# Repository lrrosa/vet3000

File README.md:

# VET 3000 — engenharia reversa e cartucho de demonstração

O **VET 3000 "The Video Effects Titler"** é um titulador de vídeo brasileiro fabricado pela
**TMS – Tecnologia em Micro Sistemas** (firmware © 1988, 1989). Por dentro, ele é um microcomputador:
CPU **Motorola MC6809**, processador de vídeo **Texas TMS9128** (família do TMS9918 usado no MSX 1 e
no ColecoVision), 16 KB de VRAM, 8 KB de RAM estática com bateria e 16 KB de ROM. O projeto deriva
do **Video Titler** publicado na revista americana *Radio-Electronics* em 1985-1986, vendido nos
EUA como **MFJ-1480B "Video Effects Titler (VET)"**.

Este repositório reúne tudo o que foi levantado sobre o aparelho:

- **Hardware:** fotos da placa, lista de componentes, mapa de memória, pinagem do conector
  traseiro CN1 e matriz do teclado.
- **Firmware v2.1:** *disassembly* completo e comentado, que **remonta byte a byte idêntico** à EPROM
  original.
- **Interface de cartucho:** o firmware procura cartuchos `"OBJECT"` e `"FONT"` no conector
  traseiro durante o boot. Aqui está documentado como escrever programas para ele.
- **Cartucho de demonstração**, com abertura animada e o jogo **QUEBRA-TIJOLO**, testado no MAME.
- **Placa do cartucho** em KiCad 10 (esquemático, placa roteada com Freerouting, Gerbers prontos),
  com EPROM 27C128 e soquete de borda para o CN1.
- **Esquema aproximado da placa principal** em KiCad 10: a parte digital, com cada ligação marcada
  como medida no aparelho ou tirada da revista, e um roteiro de continuidade.
- **Ferramentas:** disassembler 6809 com rastreamento, script Lua que simula o cartucho no MAME sem
  recompilá-lo, e um patch para o driver do MAME.

| Titulador original (MAME) | Demo: abertura | Demo: jogo |
|---|---|---|
|  |  |  |

## Principais descobertas

- **Origem:** o VET 3000 é uma versão do "Build This Video Titler", de Jack Flack
  (*Radio-Electronics*, 11/1985 a 03/1986), que a MFJ vendia como MFJ-1480B. Coincidem os CIs, o
  mapa de memória, a decodificação, a ordem dos pinos do CN1, o teclado, os registradores do VDP, os
  comandos, a abertura e a fonte. O esquema da revista explica a parte analógica e o PLL que gera o
  clock de 10,738635 MHz do VDP. O CI raspado U19 é um processador de croma CA3126 (confirmado pelas ligações). Ver
  [docs/origem.md](docs/origem.md).
- **Memória:** RAM em `$0000-$1FFF` (8 KB — a HY6264 tem 64 Kbit), cartucho em `$4000-$7FFF`,
  E/S em `$8000-$8002` e ROM em `$C000-$FFFF`. Detalhes em [docs/mapa-de-memoria.md](docs/mapa-de-memoria.md).
- **Boot automático de cartucho:** no boot, a ROM compara `"OBJECT"` em `$4000` (e depois em `$6000`)
  e executa `LDX [base+6]` / `JSR base,X`. Como o indireto lê duas vezes, `base+6` precisa conter um
  *ponteiro* para a palavra com o deslocamento da entrada. Cartuchos `"FONT"` substituem as fontes.
  Ver [docs/programando-cartuchos.md](docs/programando-cartuchos.md).
- **Uso da RAM:** o firmware nunca habilita interrupções. Os vetores de IRQ/SWI apontam para RAM
  (`$0039/$003B/$003D`) e existem só para os cartuchos. Os títulos ficam em `$00A0-$018F` e
  `$0200-$1FFF` (30 páginas); um cartucho pode rodar sem apagá-los.
- **Sem interrupção de quadro:** o `/INT` do VDP não está ligado ao `/IRQ` do 6809 (medido). Para
  sincronizar com o quadro, é preciso ler o status do VDP em laço. O driver do MAME 0.289 liga os
  dois, então um programa que dependa dessa interrupção roda no emulador e trava no aparelho. O
  patch em [mame/](mame/) corrige isso.
- **Código enxuto:** o código ocupa só cerca de 4,5 KB. O resto da ROM são três fontes (16×24, 8×24 e
  8×8), sprites e o logotipo. Há **3,2 KB livres** na EPROM.
- **Tecla "C" amarela:** não tem função no firmware v2.1 (a coluna dos modificadores só é lida nas
  linhas 1, 2 e 7, e o "C" amarelo fica na linha 6).
- **Bug no MAME 0.289:** o driver `vet3000` usa 3,58 MHz como clock do TMS9128. A tela roda a **20 Hz**
  em vez de 60 Hz. Há um patch em [mame/](mame/).

## Estrutura

```
docs/                 documentação (hardware, origem, memória, CN1, teclado, firmware, cartuchos, MAME)
  img/                fotos reduzidas, fontes extraídas da ROM e capturas de tela
  medidas-originais/  anotações originais da pinagem do CN1 e do teclado
photos/               fotos originais em alta resolução
rom/                  dump da EPROM 27128 (VET 2.1), preservado como material histórico
jogar_no_mame.bat     roda a demo no MAME (Windows)
disasm/               disassembly comentado (vet3000_v2.1.asm), anotações (hints.py), cobertura
tools/                dis6809.py, m6809.py, render_rom_gfx.py, show.py; mame/ (script Lua do cartucho)
cartridge/demo/       fonte do cartucho de demonstração (asm6809) e imagem pronta para a EPROM
mame/                 patch do driver vet3000 (slot de cartucho + clock correto do VDP)
hardware/cartucho/    projeto KiCad do cartucho (EPROM 27C128), Gerbers e scripts geradores
hardware/placa-principal/  esquema aproximado da placa principal (KiCad), roteiro de continuidade
```

## Uso rápido

Requisitos: Python 3 (com Pillow para as imagens) e o [asm6809](https://www.6809.org.uk/asm6809/).

**Conferir o disassembly** (gera o `.asm` e remonta; o resultado tem que ser idêntico à ROM):

```bash
python tools/dis6809.py rom/VET2.1-TMS_VET3000_27128A.BIN --hints disasm/hints.py -o disasm/vet3000_v2.1.asm
asm6809 -B -o /tmp/vet.bin disasm/vet3000_v2.1.asm && cmp /tmp/vet.bin rom/VET2.1-TMS_VET3000_27128A.BIN
```

**Montar o cartucho** (gera `build/vet3000_demo.bin`, com 16 KB, para uma EPROM 27128):

```bash
cd cartridge/demo && ./build.sh          # ou .\build.ps1 no Windows
```

**Rodar no MAME**, sem recompilar: o script Lua simula o cartucho no conector CN1. No Windows,
basta dar dois cliques em **`jogar_no_mame.bat`**. Ele prefere o build corrigido em
`../mame-build/vet.exe`, quando disponível, para rodar a aproximadamente 60 Hz.
Isso reduz os saltos da raquete de 9 para 3 pixels por quadro, mantendo a velocidade.
Para escolher outro MAME, passe o caminho como argumento ou defina a variável `MAME`.
Sem o build local, usa o caminho padrão configurado no `.bat`. O `.bat` chama:

```powershell
.\tools\mame\run_cart.ps1 -Mame C:\mame\mame.exe -Cart cartridge\demo\vet3000_demo.bin
```

Controles da demo: **ESPAÇO** joga, **Z/X** (ou O/P, ou ←→ com e sem SHIFT) movem a raquete,
**RETURN** pausa, **V** sobrepõe ao vídeo externo e **EXT MODE** volta ao titulador. Segurar
**EXT MODE** ao ligar pula o cartucho. No editor do titulador, **CONTROL+BORDER BLK** volta à demo
(no MAME, Ctrl esquerdo + vírgula).

## Documentação

1. [Hardware](docs/hardware.md): placa, componentes, clocks, vídeo, fonte
2. [Origem](docs/origem.md): o Video Titler da *Radio-Electronics* e o MFJ-1480B, comparação completa
3. [Mapa de memória](docs/mapa-de-memoria.md): CPU, E/S, VRAM, variáveis de RAM, ROM
4. [Conector CN1 e cartucho](docs/conector-cn1.md): pinagem e circuito de um cartucho com 27C128
5. [Teclado](docs/teclado.md): matriz, códigos, modificadores, leitura por software
6. [Firmware v2.1](docs/firmware.md): boot, laço principal, comandos, conjunto de caracteres, fontes
7. [Programando cartuchos](docs/programando-cartuchos.md): cabeçalho, regras de RAM, temporização do VDP
8. [MAME](docs/mame.md): como rodar, script Lua, bugs encontrados e patch do driver
9. [Cartucho de demonstração](cartridge/demo/README.md): técnicas, orçamento de ciclos, controles
10. [Placa do cartucho (KiCad)](hardware/cartucho/README.md): circuito, jumpers, montagem, fabricação
11. [Esquema da placa principal (KiCad)](hardware/placa-principal/README.md): parte digital e roteiro de continuidade

## Licença

Copyright © 2026 **Leonardo Roman da Rosa**.

Ferramentas, anotações do disassembly, documentação e o cartucho de demonstração são software livre
sob a **GNU General Public License versão 3** ou (a seu critério) qualquer versão posterior. Veja
[LICENSE](LICENSE).

O projeto de hardware do cartucho ([hardware/cartucho](hardware/cartucho/)) é hardware aberto sob a
**CERN-OHL-S-2.0** ([hardware/cartucho/LICENSE](hardware/cartucho/LICENSE)).

O firmware original (a imagem em `rom/` e o código e os dados reproduzidos no disassembly) é
© 1988, 1989 TMS – Tecnologia em Micro Sistemas. A empresa não existe mais, e o dump, extraído de um
aparelho real, está incluído como **material histórico, para preservação e estudo**. Ele não é
coberto pela GPL. VET 3000 e TMS são marcas dos respectivos donos. O patch do MAME segue a licença do
MAME (GPL-2.0+).

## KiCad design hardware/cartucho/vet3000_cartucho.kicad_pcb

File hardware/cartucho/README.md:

# Cartucho de ROM para o VET 3000 (KiCad)

Projeto KiCad 10 do cartucho que encaixa no conector traseiro **CN1** do VET 3000 e roda a
[demo](../../cartridge/demo/) (ou qualquer programa com cabeçalho `"OBJECT"`/`"FONT"`).

Copyright © 2026 Leonardo Roman da Rosa. Hardware aberto sob a **CERN-OHL-S-2.0** (ver
[Licença](#licença)).

| Frente (componentes, voltada para o VET) | Verso (fica à vista) | 3D |
|---|---|---|
|  |  |  |

## Arquivos

| Arquivo | Conteúdo |
|---|---|
| `vet3000_cartucho.kicad_pro/.kicad_sch/.kicad_pcb` | Projeto KiCad (esquemático, placa roteada) |
| `vet3000.pretty/` | Footprint do soquete de borda 2×18 (gerado por `gen/gen_footprint.py`) |
| `fabricacao/vet3000_cartucho_gerbers.zip` | Gerbers + furação para enviar à fábrica |
| `fabricacao/vet3000_cartucho_esquematico.pdf` | Esquemático em PDF |
| `fabricacao/vet3000_cartucho_bom.csv` | Lista de materiais |
| `fiacao-prototipo.svg` | Diagrama de fiação para montar em placa protótipo de uma face (gerado por `gen/gen_fiacao.py`, conferido contra o netlist) |
| `gen/` | Scripts que geram tudo (ver "Regenerar") |

Verificação: ERC sem violações; DRC sem violações, sem pads desconectados e com paridade
esquemático↔placa (`kicad-cli pcb drc --schematic-parity`). Placa de 2 camadas, 72 × 60 mm, trilhas
de 0,25 mm (sinais) e 0,6 mm (alimentação), isolação de 0,2 mm, planos de GND nas duas faces.
Roteada com o Freerouting.

## Circuito

- **J1**: soquete fêmea de borda 2×18 que encaixa nos dedos do CN1. A fileira **a** toca os
  contatos de cima do CN1 (face de componentes do VET: IRQ, D0-D7, seleções, R/W, HALT, +5V, GND);
  a fileira **b** toca os de baixo (A0-A13, GND). **b1 (+3 V da bateria) e b16 (−5 V) não são
  ligados.**
- **U1**: EPROM 27C128 (16 KB) em soquete. `/CE` = seleção **Y1** do VET (`$4000-$7FFF`, contato
  a14), passando pelo jumper **JP3**.
- **U2**: 74HCT00 fazendo `/OE = NÃO(R/W)`: a EPROM só coloca dados no barramento em leituras, e
  uma escrita por engano em `$4000-$7FFF` não causa conflito. As outras três portas ficam com as
  entradas no GND.
- **R1** (10k): mantém `/CE` em 1 com o JP3 aberto.
- **J2 (EXP)**: +5V, IRQ, HALT, R/W, Y2 (`$8000-$BFFF`), E da ROM interna, 1G e GND, para
  experiências (E/S externa, depuração).

## Jumpers

| Memória | JP1 (pino 1) | JP2 (pino 27) |
|---|---|---|
| **27C128** (padrão) | 2-3 (VPP = +5 V) | 2-3 (/PGM = +5 V) |
| 27C256 | 2-3 (VPP = +5 V) | A14: 1-2 = metade de baixo, 2-3 = metade de cima |
| W27C512 / 27C512 | A15 | A14 (juntos escolhem um de 4 bancos de 16 KB) |
| 28C256 (EEPROM) | A14: escolhe a metade | 2-3 (/WE = +5 V, nunca escreve) |

**JP3 fechado** = cartucho ativo. **Aberto** = o VET não enxerga o cartucho e liga direto no
titulador. Com a demo dá para fazer o mesmo sem mexer no jumper: segure EXT MODE ao ligar. Depois,
CONTROL+BORDER BLK no editor do titulador chama a demo.

Para gravar: a imagem `cartridge/demo/vet3000_demo.bin` tem 16 KB e vai direto na 27C128. Numa
27C256/27C512, grave-a na metade ou banco escolhido pelos jumpers (ex.: duplicada nas duas metades).

## Montagem mecânica

O CN1 do VET são **dedos de borda** na própria placa principal (macho). O cartucho usa um
**soquete fêmea reto**, e a placa fica **em pé atrás do aparelho, com os componentes voltados
para o VET**. Assim, olhando o VET por trás, o pino 1 fica à esquerda, como na medida original.
Na serigrafia: "COMPONENTES VOLTADOS PARA O VET" na frente e "ESTE LADO PARA FORA" no verso.

## Antes de mandar fabricar

- **Passo dos dedos do CN1: 2,54 mm (0,1"), medido** no aparelho. É o passo do footprint.
- **Soquete:** o footprint supõe soquete de 0,1" com terminais em duas fileiras a **5,08 mm**
  (0,2"), como o Sullins EBC18DCxN. Confira no datasheet do soquete comprado.
- **Espaço atrás do VET:** a abertura do painel, o comprimento dos dedos para fora e se a placa
  de 72 × 60 mm em pé não bate em nada.
- Opcional: com ponta lógica, confirmar que o contato a14 (Y1) só vai a 0 nos acessos a
  `$4000-$7FFF`.

Se o soquete tiver outra distância entre fileiras, gere o footprint com a medida certa
(`python gen/gen_footprint.py 2.54 3.56`, por exemplo), recrie a placa e roteie de novo (abaixo).

## Lista de materiais

| Ref. | Peça |
|---|---|
| J1 | Soquete de borda fêmea 0,1", 2×18 (36 vias), terminais para PCI |
| U1 | EPROM 27C128 (ou 27C256, W27C512, 28C256) + soquete DIP-28 600 mil |
| U2 | 74HCT00 + soquete DIP-14 |
| C1, C2 | 100 nF cerâmico, passo 5 mm |
| C3 | 10 µF 16 V eletrolítico, Ø5 mm, passo 2 mm |
| R1 | 10 kΩ 1/4 W |
| JP1, JP2 | Barra de pinos 1×3 + jumper |
| JP3 | Barra de pinos 1×2 + jumper |
| J2 | Barra de pinos 1×8 (opcional) |

Placa: 2 camadas, FR-4 1,6 mm, 72 × 60 mm, furos de 1,0 mm (pads) e 0,4 mm (vias), 2 furos M3.

## Regenerar

Os scripts em `gen/` geram o projeto do zero. Rode-os a partir desta pasta:

```bash
python gen/gen_footprint.py            # footprint do soquete (passo e fileiras como argumentos)
python gen/gen_project.py              # .kicad_pro (classes de rede) e fp-lib-table
python gen/gen_schematic.py            # esquemático
kicad-cli sch erc vet3000_cartucho.kicad_sch
kicad-cli sch export netlist --format kicadsexpr -o vet3000_cartucho.net vet3000_cartucho.kicad_sch
"C:/Program Files/KiCad/10.0/bin/python.exe" gen/gen_pcb.py   # ATENÇÃO: recria a placa sem trilhas
python gen/gen_fiacao.py               # diagrama de fiação da placa protótipo (lê o .net)
```

Roteamento (caminhos **sem espaços** para o Freerouting):

```bash
PY="C:/Program Files/KiCad/10.0/bin/python.exe"; W=C:/Temp/fr
"$PY" gen/route.py decoy vet3000_cartucho.kicad_pcb $W/isca.kicad_pcb   # sem zonas, borda recuada
"$PY" gen/route.py export $W/isca.kicad_pcb $W/rota.dsn
"$PY" gen/route.py tweak $W/rota.dsn 250 600 200   # sinais 0,25, +5V/GND 0,6, isolação 0,2 mm
freerouting.exe -de $W/rota.dsn -do $W/rota.ses -mp 300 -mt 1
"$PY" gen/route.py import vet3000_cartucho.kicad_pcb $W/rota.ses    # trilhas + preenche zonas
kicad-cli pcb drc --schematic-parity --severity-all vet3000_cartucho.kicad_pcb
```

A etapa `tweak` move +5V e GND para uma classe "power" mais larga no DSN, com as mesmas regras
do `.kicad_pro`.

Fabricação:

```bash
kicad-cli pcb export gerbers --layers "F.Cu,B.Cu,F.SilkS,B.SilkS,F.Mask,B.Mask,Edge.Cuts" --subtract-soldermask -o fabricacao/gerbers/ vet3000_cartucho.kicad_pcb
kicad-cli pcb export drill --format excellon --drill-origin absolute --excellon-units mm --generate-map --map-format gerberx2 -o fabricacao/gerbers/ vet3000_cartucho.kicad_pcb
```

## Licença

Copyright © 2026 Leonardo Roman da Rosa.

Esta fonte descreve Hardware Aberto e é licenciada sob a CERN-OHL-S v2 ([LICENSE](LICENSE)). Você
pode redistribuir e modificar esta fonte e fabricar produtos com ela nos termos da CERN-OHL-S v2
(https://ohwr.org/cern_ohl_s_v2.txt).

Esta fonte é distribuída SEM QUALQUER GARANTIA EXPRESSA OU IMPLÍCITA, INCLUSIVE DE
COMERCIABILIDADE, QUALIDADE SATISFATÓRIA E ADEQUAÇÃO A UM FIM ESPECÍFICO. Veja as condições
aplicáveis na CERN-OHL-S v2.

Source location: https://github.com/lrrosa/vet3000

Conforme a seção 4 da CERN-OHL-S v2, quem fabricar hardware a partir desta fonte deve, quando
possível, manter o Source Location visível no exterior do produto. A serigrafia do verso da placa
já traz o endereço.

A licença vale para tudo nesta pasta: esquemático, placa, footprint, arquivos de fabricação e os
scripts de `gen/`, que são a fonte do projeto. O restante do repositório (ferramentas, disassembly
e o software da demo) segue sob a GPL-3.0-or-later.

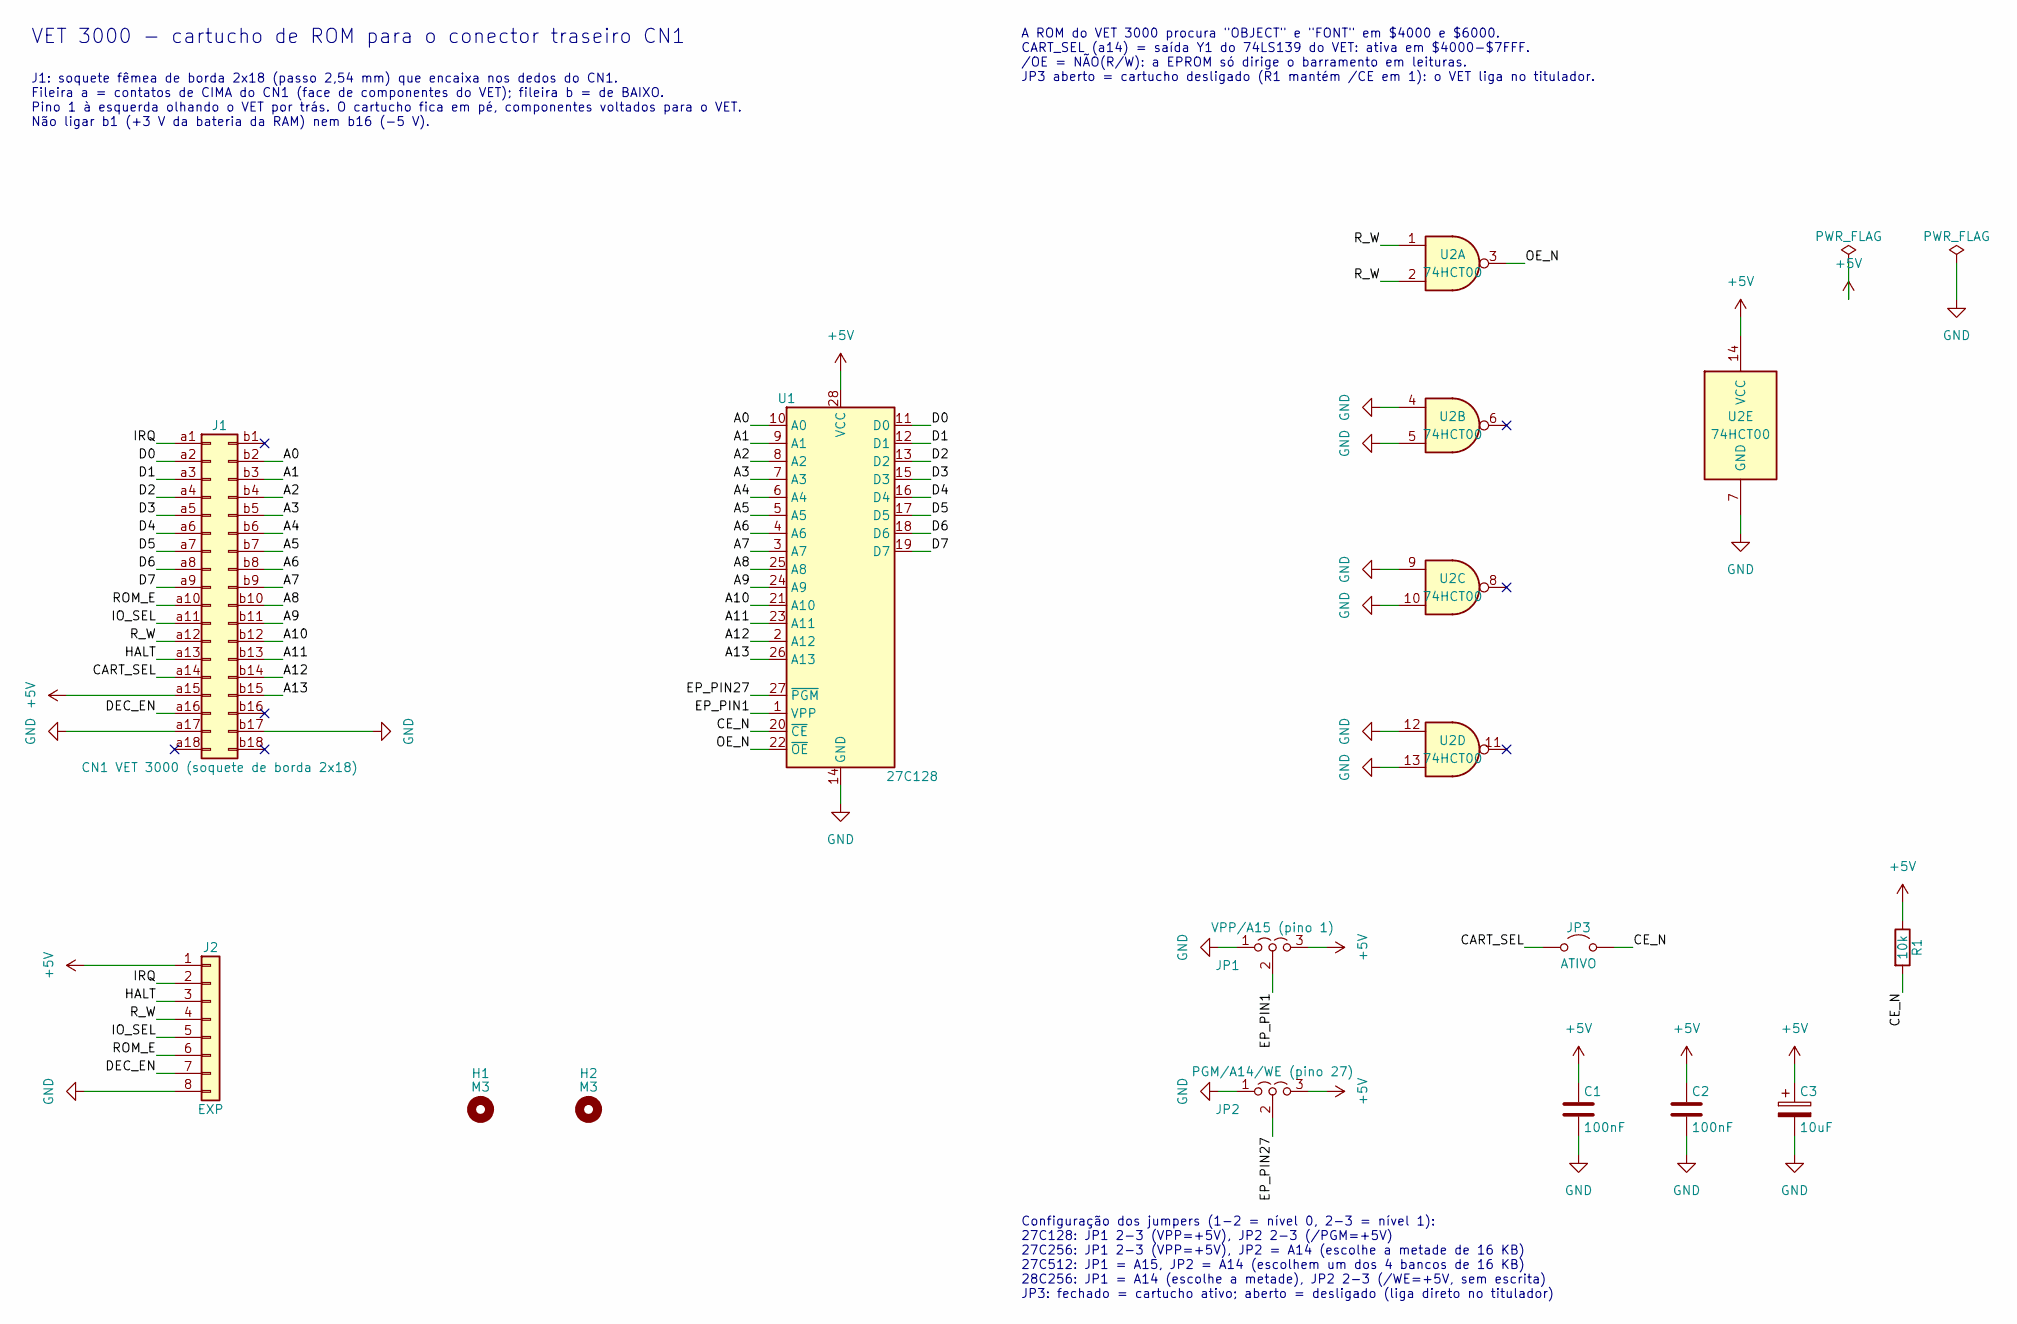
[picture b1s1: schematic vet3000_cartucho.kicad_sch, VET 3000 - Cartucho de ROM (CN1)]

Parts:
C1, C2: 100nF; C_Disc_D5.0mm_W2.5mm_P5.00mm
C3: 10uF; CP_Radial_D5.0mm_P2.00mm
H1, H2: M3; MountingHole_3.2mm_M3
J1: CN1 VET 3000 (soquete de borda 2x18); CardEdge_Socket_2x18_P2.54mm_Row5.08mm
J2: EXP; PinHeader_1x08_P2.54mm_Vertical
JP1: VPP/A15 (pino 1); PinHeader_1x03_P2.54mm_Vertical
JP2: PGM/A14/WE (pino 27); PinHeader_1x03_P2.54mm_Vertical
JP3: ATIVO; PinHeader_1x02_P2.54mm_Vertical
R1: 10k; R_Axial_DIN0207_L6.3mm_D2.5mm_P7.62mm_Horizontal
U1: 27C128; DIP-28_W15.24mm_Socket
U2: 74HCT00; DIP-14_W7.62mm_Socket

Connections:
+5V: C1.1, C2.1, C3.1, J1.a15, J2.1, JP1.3 (B), JP2.3 (B), R1.1, U1.28 (VCC), U2.14 (VCC)
/A0: J1.b2, U1.10 (A0)
/A1: J1.b3, U1.9 (A1)
/A2: J1.b4, U1.8 (A2)
/A3: J1.b5, U1.7 (A3)
/A4: J1.b6, U1.6 (A4)
/A5: J1.b7, U1.5 (A5)
/A6: J1.b8, U1.4 (A6)
/A7: J1.b9, U1.3 (A7)
/A8: J1.b10, U1.25 (A8)
/A9: J1.b11, U1.24 (A9)
/A10: J1.b12, U1.21 (A10)
/A11: J1.b13, U1.23 (A11)
/A12: J1.b14, U1.2 (A12)
/A13: J1.b15, U1.26 (A13)
/CART_SEL: J1.a14, JP3.1 (A)
/CE_N: JP3.2 (B), R1.2, U1.20 (~CE)
/D0: J1.a2, U1.11 (D0)
/D1: J1.a3, U1.12 (D1)
/D2: J1.a4, U1.13 (D2)
/D3: J1.a5, U1.15 (D3)
/D4: J1.a6, U1.16 (D4)
/D5: J1.a7, U1.17 (D5)
/D6: J1.a8, U1.18 (D6)
/D7: J1.a9, U1.19 (D7)
/DEC_EN: J1.a16, J2.7
/EP_PIN1: JP1.2 (C), U1.1 (VPP)
/EP_PIN27: JP2.2 (C), U1.27 (~PGM)
/HALT: J1.a13, J2.3
/IO_SEL: J1.a11, J2.5
/IRQ: J1.a1, J2.2
/OE_N: U1.22 (~OE), U2.3
/ROM_E: J1.a10, J2.6
/R_W: J1.a12, J2.4, U2.1, U2.2
GND: C1.2, C2.2, C3.2, J1.a17, J1.b17, J2.8, JP1.1 (A), JP2.1 (A), U1.14 (GND), U2.4, U2.5, U2.7 (GND), U2.9, U2.10, U2.12, U2.13

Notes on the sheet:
VET 3000 - cartucho de ROM para o conector traseiro CN1
J1: soquete fêmea de borda 2x18 (passo 2,54 mm) que encaixa nos dedos do CN1. Fileira a = contatos de CIMA do CN1 (face de componentes do VET); fileira b = de BAIXO. Pino 1 à esquerda olhando o VET por trás. O cartucho fica em pé, componentes voltados para o VET. Não ligar b1 (+3 V da bateria da RA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
A ROM do VET 3000 procura "OBJECT" e "FONT" em $4000 e $6000. CART_SEL (a14) = saída Y1 do 74LS139 do VET: ativa em $4000-$7FFF. /OE = NÃO(R/W): a EPROM só dirige o barramento em leituras. JP3 aberto = cartucho desligado (R1 mantém /CE em 1): o VET liga no titulador.
Configuração dos jumpers (1-2 = nível 0, 2-3 = nível 1): 27C128: JP1 2-3 (VPP=+5V), JP2 2-3 (/PGM=+5V) 27C256: JP1 2-3 (VPP=+5V), JP2 = A14 (escolhe a metade de 16 KB) 27C512: JP1 = A15, JP2 = A14 (escolhem um dos 4 bancos de 16 KB) 28C256: JP1 = A14 (escolhe a metade), JP2 2-3 (/WE=+5V, sem escrit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

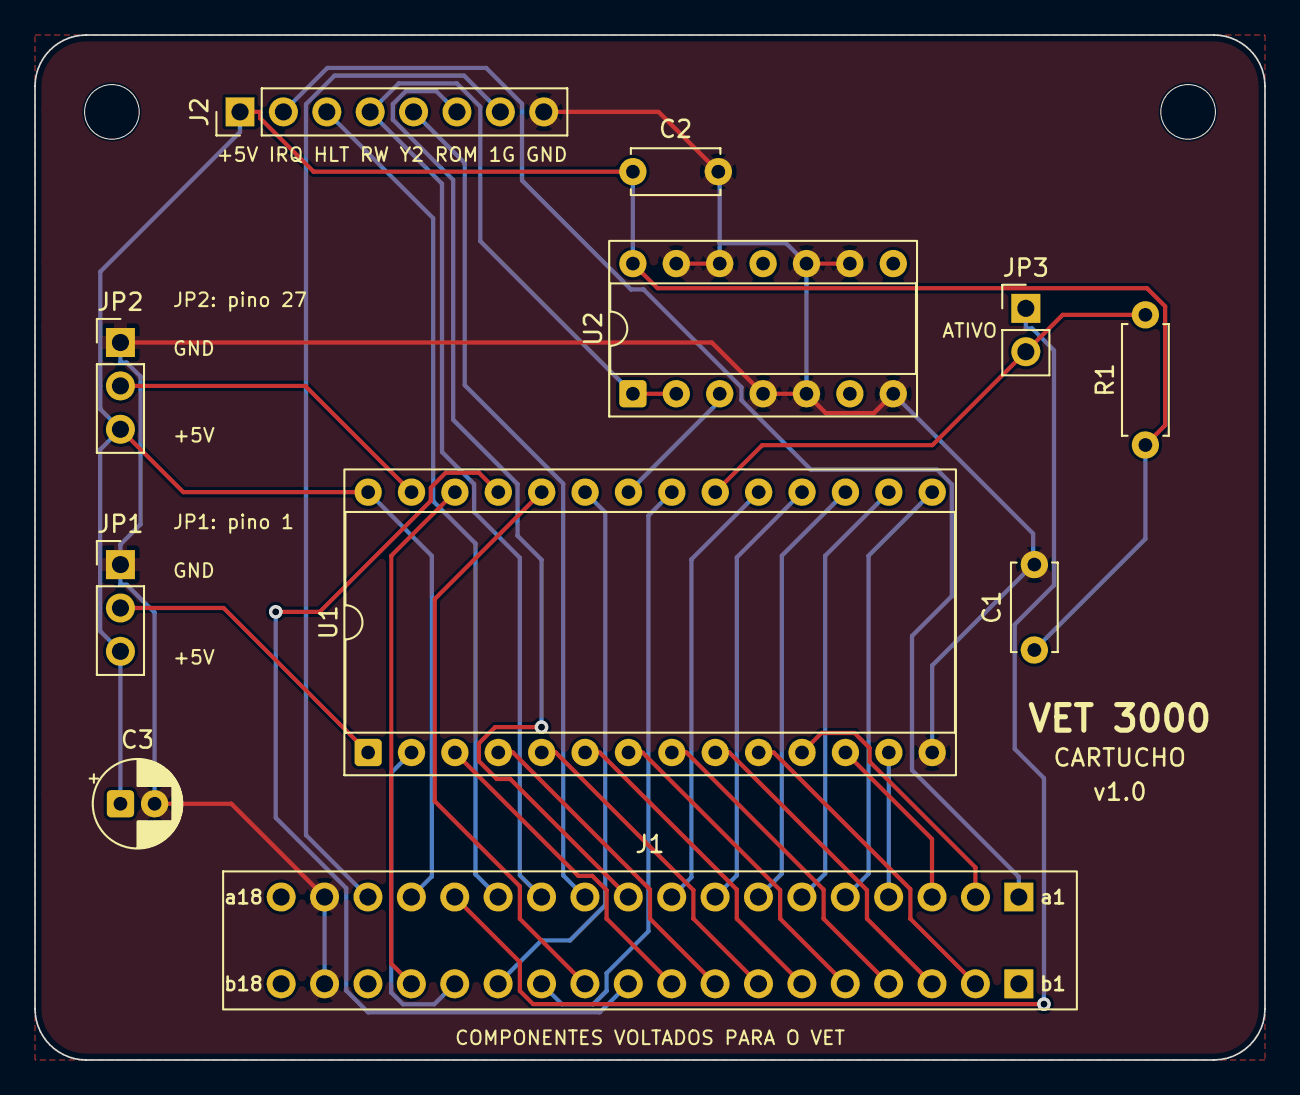
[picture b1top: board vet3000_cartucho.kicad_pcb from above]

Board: 2 copper layers, 72.0 x 60.0 mm, 13 parts (0 on the bottom side), 35 nets.

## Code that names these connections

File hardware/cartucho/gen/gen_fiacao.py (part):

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net("OE_N", C_CTRL, ("U2", "3"), ("U1", "22"))
net("CART_SEL", C_CTRL, ("J1", "a14"), ("JP3", "1"))
net("CE_N", C_CTRL, ("JP3", "2"), ("U1", "20"), ("R1", "2"))
net("EP_PIN1", C_JMP, ("JP1", "2"), ("U1", "1"))
net("EP_PIN27", C_JMP, ("JP2", "2"), ("U1", "27"))
net("IRQ", C_EXP, ("J1", "a1"), ("J2", "2"))
net("HALT", C_EXP, ("J1", "a13"), ("J2", "3"))
net("IO_SEL", C_EXP, ("J1", "a11"), ("J2", "5"))
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
# nomes curtos (como no conector-cn1.md e na serigrafia da PCI)
SHORT = {"R_W": "R/W", "OE_N": "/OE", "CE_N": "/CE", "CART_SEL": "Y1", "IO_SEL": "Y2", "ROM_E": "E",
         "DEC_EN": "1G", "EP_PIN1": "VPP", "EP_PIN27": "/PGM"}


def short(n):
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    return out


ORDER = ["OE_N", "R_W", "CE_N", "CART_SEL", "EP_PIN1", "EP_PIN27", "GND", "+5V"]
for n in ORDER:
    pins = [k for k in NETS[n][1] if PINS[k][2] is not None and k not in LABEL_ONLY]
    if n in RAILS:
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

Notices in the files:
hardware/cartucho/gen/gen_fiacao.py:
Copyright (C) 2026 Leonardo Roman da Rosa
SPDX-License-Identifier: CERN-OHL-S-2.0
Hardware aberto sob a CERN-OHL-S v2 (ver hardware/cartucho/LICENSE).
hardware/cartucho/vet3000_cartucho.kicad_pcb:
Copyright (C) 2026 Leonardo Roman da Rosa - CERN-OHL-S-2.0
